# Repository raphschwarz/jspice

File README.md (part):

## JSpice for Mac

A native macOS app with a drag-and-draw schematic editor and live, real-time simulation (like iCircuit or Falstad) is in [`macos/`](macos/README.md).

## Introduction

JSpice is a SPICE-inspired analog circuit simulator made in Java with an emphasis on simulating memristors and analog circuits containing memristors. 

In a nutshell, JSpice is very limited compared to mainstream SPICE versions and only can do the following:

1. DC Operating Point Analysis
2. DC Sweep Analysis
3. Transient Analysis (Time response to arbitrary input waveform)

JSpice was originally written at a time before any mainstream SPICE applications supported simulation of memristors, and at that point we felt it would be easier to write a custom version of SPICE in Java rather than to try to figure out how to natively integrate memristor devices into existing SPICE versions. More recently, other, more capable simulators such as Xyce, have appeared with [native support for memristors](http://knowm.org/native-memristor-device-development-in-xyce/), and we are now leveraging those tools for CMOS + memristor circuit simulations.

JSpice is however still useful for rapid prototyping and serves as the simulation engine for [memristor-discovery](https://github.com/knowm/memristor-discovery). JSpice may interest you if you are interested in learning the mechanics of modified nodal analysis and your favorite programming langauge is Java. 

## Flow Chart of JSpice

Following is a simplified block diagram of the main JSpice program flow. 

)](documentation/SPICE_flow_chart.png)  

### In Words

- while the simulation is not over  
    * Formulate companion models for energy storage components, using current operating point  
    * Newton loop :  
        * while the convergence is not achieved  
            - Formulate companion models for non−linear components, using current operating point  
            - Solve for new operating point  
        * end while   
- end while  

([source](http://dev.hypertriton.com/edacious/trunk/doc/lec.pdf))

The heart of JSpice is matrix multiplication to solve the node values.

## Linear DC Operating Point Analysis

The core of any circuit simulation software is DC Operating Point Analysis. It's required for an initial solution to a Transient Analysis and also at each time step of a DC Sweep Analysis. All energy-storage components like capacitors, inductors and semiconductor charge mechanisms are ignored for this analysis. To perform a very basic DC Operating Point Analysis, the circuit Netlist needs to be loaded and parsed followed by solving linear nodal equations for voltage at each node:

1. Import Netlist
1. AC sources are zeroed out, capacitors are opened, and inductors are shorted
1. Use Kirchhoff's current law (KCL) to determine the algebraic sum of currents at each node
1. Using Linear Algebra, solve for the voltages at each node: G • v = i, where G is the conductance coefficients, v and i is the voltage and current at each node respectively.

A computerized circuit solver like SPICE doesn't start by writing nodal equations and converting them into a matrix. An advanced technique called Modified Nodal Analysis (MNA) is used. Each device has an MNA Stamp which is directly inserted into the impedance matrix (G) and the fixed source matrix (also called the right-hand-side matrix, RHS). Each voltage node and voltage source has a row/column pair and a slot in the RHS matrix. Each device is provided with pointers to locations in the matrix that it effects. That way a device doesn't have to have knowledge of the entire circuit, just the nodes it effects.

Like SPICE since version 3f5, JSpice uses MNA for Nodal Analysis, and it uses LUDecomposition to solve the systems of linear equations to determine the nodal values. For more information about MNA and MNA Stamps see the following links:

1. <http://users.ecs.soton.ac.uk/mz/CctSim/contents.htm>
1. <http://www.ece.iisc.ernet.in/~dipanjan/E8_262/E8262-CAD_4+5.pdf>
1. <http://qucs.sourceforge.net/tech/technical.html>
1. <http://dev.hypertriton.com/edacious/trunk/doc/lec.pdf>
1. <http://qucs.sourceforge.net/tech/node14.html>
1. <http://users.ecs.soton.ac.uk/mz/CctSim/chap1_3.htm>
1. <http://users.ecs.soton.ac.uk/mz/CctSim/chap1_4.htm>
1. <https://www.scribd.com/document/277142543/MNA-Stamp>

The above formulation of MNA can be applied to linear circuits only, but can extend to nonlinear. A linear circuit is an electronic circuit in which, for a sinusoidal input voltage of frequency f, any steady-state output of the circuit (the current through any component, or the voltage between any two points) is also sinusoidal with frequency f. Note that the output need not be in phase with the input.

The costs of the automatic circuit equation formulation:

1. To parse the Netlist : It consists in reading and storing the Netlist. O(N).
1. A topological analysis to build the unknowns vector: The Minimum Spanning Tree algorithm complexity is O(Nlog(N))
1. Stamping method: Each component writes its contribution in the table equation. O(N).
1. Matrix product: Multiplied two dense matrices costs O(N^3).

### Linear DC Operating Point Analysis Examples

#### I1R3 - One Current Source and Three Resistors

##### Code

Here, the `NetlistBuilder` pattern is demonstrated.

```java
public class DCOPI1R3 {

  public static void main(String[] args) {

    // run via NetlistBuilder
    NetlistBuilder builder = new NetlistBuilder().addNetlistDCCurrent("a", 1.0, "0", "1").addNetlistResistor("R1", 10, "1", "0")
        .addNetlistResistor("R2", 1000, "1", "2").addNetlistResistor("R3", 1000, "2", "0");
    Netlist netlist = builder.build();
    JSpice.simulate(netlist);
  }
}
```

##### Result

```
----nodes----
V(1) = 9.950248756218906
V(2) = 4.975124378109452
----components----
I(R1) = 0.9950248756218907
I(R2) = 0.004975124378109454
I(R3) = 0.004975124378109453
I(a) = 1.0
-------------
```

#### I1V1R6 -  One Current Source, One Voltage Source and Six Resistors

##### Code

Here, the `Netlist` is created as a stand-alone class, ideal for circuit reuse.

```java
public class DCOPI1V1R6 {

  public static void main(String[] args) {

    Netlist netlist = new I1V1R6();
    JSpice.simulate(netlist);
  }
}
```

```java
public class I1V1R6 extends Netlist {

  public I1V1R6() {

    // build netlist, the nodes can be named anything except for ground whose node is always labeled "0"
    addNetListComponent(new NetlistDCCurrent("a", 0.02, "0", "4"));
    addNetListComponent(new NetlistDCVoltage("x", 10.0, "2", "5"));
    addNetListComponent(new NetlistResistor("R1", 100, "5", "0"));
    addNetListComponent(new NetlistResistor("R2", 1000, "0", "3"));
    addNetListComponent(new NetlistResistor("R3", 1000, "2", "3"));
    addNetListComponent(new NetlistResistor("R4", 100, "1", "2"));
    addNetListComponent(new NetlistResistor("R5", 1000, "3", "0"));
    addNetListComponent(new NetlistResistor("R6", 10000, "1", "4"));
  }
}
```

##### Result

```
----nodes----
I(x) = 0.01250000000000003
V(1) = 13.250000000000005
V(2) = 11.250000000000004
V(3) = 3.750000000000001
V(4) = 213.25
V(5) = 1.2500000000000029
----components----
I(R1) = 0.012500000000000028
I(R2) = -0.0037500000000000007
I(R3) = 0.007500000000000002
I(R4) = 0.020000000000000018
I(R5) = 0.0037500000000000007
I(R6) = -0.02
I(a) = 0.02
-------------
```

## DC Sweep Analysis

DC Sweep Analysis is used to calculate a circuit’s bias point over a range of values. This procedure allows you to simulate a circuit many times, sweeping the DC values within a predetermined range. You can control the source values by choosing the start and stop values and the increment for the DC range. The bias point of the circuit is calculated for each value of the sweep.   

JSpice performs DC Sweep Analysis using the following process:

1. The DC Operating Point is calculated using a specified start value.
1. The value from the source is incremented and another DC Operating Point is calculated.
1. The increment value is added again and the process continues until the stop value is reached.
1. The result is displayed in a chart.

Assumptions: Capacitors are treated as open circuits, inductors as shorts. Only DC values for voltage and current sources are used.

All energy-storage components like capacitors, inductors and semiconductor charge mechanisms are ignored for this analysis. When time-varying components are present, their long-term behavior is approximated for example, capacitors become open circuits, and inductors become short circuits.

#### DC Sweep V1R4 - One Voltage Source and Four Resistors

##### Code

```java
public class DCSweepV1R4 {

  public static void main(String[] args) {

    Netlist netlist = new V1R4();
    netlist.setSimulationConfig(new DCSweepConfig("R1", "I(3)", 100.0, 10000, 100));
    JSpice.simulate(netlist);
  }
}
```

##### Result

## Non-Linear DC Operating Point Analysis

To simulate real circuits containing transistors and diodes, we are interested in simulating components having arbitrary i-v relations. We use the standard Newton method, described in any numerical analysis textbook. The derivation of how the multidimensional Newton method leads to our algorithm is a bit tedious, but here is an intuitive explanation : the Newton method works by linearizing the equation around the operating point Xn, solving the linearized equation to obtain Xn+1, and iterating until convergence (being when Xn is near Xn+1; the precise definition of near involving a compromise between speed and accuracy). In circuits, we linearize the i-v characteristic around point vn : i = i(vn)+(dv/di)(v−vn). That allows us to form companion models describing the linearized component, which we can stamp. The equation is then solved for another operating point, and the cycle continues until a stable answer is found.

### PN Diode Companion Model

)](documentation/PN_Diode_Model.png)  

#### DCSweepV1D1 - One Voltage Source and One Diode

##### Code

```java
public class DCSweepV1D1 {

  public static void main(String[] args) {

    Netlist netlist = new V1D1();
    netlist.setSimulationConfig(new DCSweepConfig("Va", "I(D1)", 0.5, .95, .005));
    JSpice.simulate(netlist);
  }
}
```

##### Result

### MOSFET NMOS Companion Model

)](documentation/NMOS_Model.png)  

#### DCSweepV2NMOS1 - Two Voltage Sources and One NMOS

##### Code

```java
public class DCSweepV2NMOS1 {

  public static void main(String[] args) {

    // Circuit
    Netlist netlist = new V2NMOS1();

    // SweepDef
    DCSweepConfig sweepDef1 = new DCSweepConfig("Vdd", "I(NMOS1)", 0.0, 10.0, 0.1);
    DCSweepConfig sweepDef2 = new DCSweepConfig("Vg", "I(NMOS1)", 0.0, 5.0, 1.0);

    // run DC sweep
    DCSweep dcSweep = new DCSweep(netlist);
    dcSweep.addSweepConfig(sweepDef1);
    dcSweep.addSweepConfig(sweepDef2);
    SimulationResult dcSweepResult = dcSweep.run("I(NMOS1)");

    // plot
    SimulationPlotter.plotAll(dcSweepResult);

  }
}
```

##### Result

### MOSFET PMOS Companion Model

)](documentation/PMOS_Model.png)  

#### DCSweepV2PMOS1 - Two Voltage Sources and One PMOS

##### Code

```java
public class DCSweepV2PMOS1 {

  public static void main(String[] args) {

    // Circuit
    Netlist netlist = new V2PMOS1();

    // SweepDef
    DCSweepConfig sweepDef1 = new DCSweepConfig("Vg", "I(PMOS1)", -5.0, 0.0, 1.0);
    DCSweepConfig sweepDef2 = new DCSweepConfig("Vdd", "I(PMOS1)", -10.0, 0.0, 0.1);

    // run DC sweep
    DCSweep dcSweep = new DCSweep(netlist);
    dcSweep.addSweepConfig(sweepDef2);
    dcSweep.addSweepConfig(sweepDef1);
    SimulationResult dcSweepResult = dcSweep.run("I(PMOS1)");
    System.out.println(dcSweepResult.toString());

    // plot
    SimulationPlotter.plotAll(dcSweepResult);
  }
}
```

##### Result

#### CMOSInverter

##### Code

```java
public class DCSweepCMOSInverter {

  public static void main(String[] args) {

    Netlist netlist = new CMOSInverterCircuit();
    netlist.setSimulationConfig(new DCSweepConfig("Vin", "V(out)", 0, 5, .10));
    JSpice.simulate(netlist);
  }
}
```

##### Result

## Transient Analysis

In Transient Analysis, also called time-domain transient analysis, JSpice computes the circuit’s response as a function of time. This analysis divides the time into segments and calculates the voltage and current levels for each given interval. Finally, the results, voltage versus time, are plotted.

JSpice performs Transient Analysis using the following process:

Each input cycle is divided into intervals.
A DC Operating Point Analysis is performed for each time point in the cycle.
The solution for the voltage waveform at a node is determined by the value of that voltage at each time point over one complete cycle.

Assumptions: DC sources have constant values; AC sources have time-dependent values. Capacitors and inductors are represented by energy storage models. Numerical integration is used to calculate the quantity of energy transfer over an interval of time.

Let's see how numeric integration for a capacitor works. Knowing a function at some point in time `tn`, how could you approximate the function at a future time point `tn+1`? Here's one approach. What if you looked to the slope of the curve to tell you, at least locally, where the voltage is going? Then, simply multiply the slope by the time step `h = Δt = tn+1 - tn` and add it to the present voltage - that should get you in the neighborhood at least.

The FE formula is so intuitive, but its not the best method. Another method, the backward- Euler (BE), uses the slope at `xn+1`, rather than the one at `xn`, to predict the next voltage.

Okay, we're approaching our overall goal of transforming an energy-storage component into its equivalent linear components. For example, a capacitor is transformed using a two step process:

Step 1. Apply numeric integration to the current-versus-voltage relationship of a capacitor.
Step 2. Use the result to develop a linear companion memristor well-suited for Nodal Analysis to calculate the circuit's output waveform.

Long story short, given the time step size (`h`) and the voltage across the capacitor at a certain time point, the capacitor is replaced in the circuit with the following linear companion memristor consisting of a Resistor and a current source. JSpice then carries out it's nodal analysis as before.

)](documentation/Capacitor_Model.png)  

### Drivers

The following time-based drivers are available: DC, Sine, Triangle, Sawtooth, Square, Pulse, Arbitrary, and Streaming Arbitrary. Most Drivers take the following arguments during creation:

* Name
* DC Offset
* Phase
* Amplitude
* Frequency

#### DC
    Driver driver = new DC("Vdc", 2.5);

#### Sine
    Driver sine = new Sine("Sine", 5, Math.PI / 4, 10, 2);

#### Triangle
    Driver driver = new Triangle("Triangle", 5, 0.25, 10, 2);

#### Sawtooth
    Driver driver = new Sawtooth("Sawtooth", 5, .25, 10, 2);

#### Square
    Driver driver = new Square("Square", 5, .2, 10, .5); // unit test case

#### Pulse
    Driver driver = new Pulse("Pulse", 5, .2, 10, .5, .10); // unit test case

#### Arbitrary
    Driver driver = new Arbitrary("Arbitrary", 0, 0, 1, 1.0, new double[] { .1, .2, .5, .6 });

#### Arbitrary Streaming
    Driver driver = new StreamingArbitrary("Arbitrary Streaming", 0, 0, 1, 1.0, new double[] { .1, .2, .5, .6 }, new String[] { "1", "0", "1" });

#### CMOS Inverter with Triangle Driver

##### Code

```java
public class TransientAnalysisCMOSInverter {

  public static void main(String[] args) {

    Netlist netlist = new CMOSInverterCircuit();
    TransientConfig transientConfig = new TransientConfig(2, .05, new Triangle("Vin", 2.5, 0, 2.5, 1.0));
    netlist.setSimulationConfig(transientConfig);
    SimulationResult simulationResult = JSpice.simulate(netlist);
    SimulationPlotter.plot(simulationResult, "V(in)", "V(out)");
  }
}
```

##### Result

#### RC Circuit with Square Driver

##### Code

```java
public class TransientAnalysisV1R1C1 {

  public static void main(String[] args) {

    Netlist netlist = new V1R1C1();
    TransientConfig transientConfig = new TransientConfig(2, .01, new Square("V1", 2.5, 0, 2.5, 1.0));
    netlist.setSimulationConfig(transientConfig);
    SimulationResult simulationResult = JSpice.simulate(netlist);
    SimulationPlotter.plot(simulationResult, new String[]{"V(1)", "V(2)"});
  }
}
```

##### Result

#### Half-Wave Rectifier with Sine Driver

##### Code

```java
public class TransientAnalysisHalfWaveRectifier {

  public static void main(String[] args) {

    Netlist netlist = new HalfWaveRectifier();
    TransientConfig transientConfig = new TransientConfig(.0833333333, .0002, new Sine("Vsrc", 0, 0, 12, 60.0));
    netlist.setSimulationConfig(transientConfig);
    SimulationResult simulationResult = JSpice.simulate(netlist);
    SimulationPlotter.plot(simulationResult, "V(in)", "V(out)");
  }
}
```

##### Result

#### Pass Gate (Transmission Gate)

##### Code

```java
public class TransientAnalysisTransmissionGate {

  public static void main(String[] args) {

    Netlist netlist = new TransmissionGateCircuit();

    Driver in = new Sine("Vin", 0, 0, 1.0, 10.0);
    Driver clk = new Square("Vclk", 2.5, 0, 2.5, 1.0);
    Driver clkBar = new Square("VclkBar", 2.5, 0.5, 2.5, 1.0);

    TransientConfig transientConfig = new TransientConfig(2, .005, in, clk, clkBar);
    netlist.setSimulationConfig(transientConfig);
    SimulationResult simulationResult = JSpice.simulate(netlist);
    SimulationPlotter.plotSeparate(simulationResult, "V(out)", "V(in)", "V(CLK)", "V(CLKBAR)");
  }
}
```

##### Result

## M-MSS Memristor Simulation

### Simple Hysteresis Curves

#### M-MSS Memristor Model Driven by Square Wave

##### Code

```java
public class TransientAnalysisV1MMSSMem {

  public static void main(String[] args) {

    Netlist netlist = new V1MMSSMem();
    TransientConfig transientConfig = new TransientConfig(.04, .0001, new Sine("Vdd", 0.0, 0, 0.5, 100.0));
    netlist.setSimulationConfig(transientConfig);
    SimulationResult simulationResult = JSpice.simulate(netlist);
    SimulationPlotter.plotSeparate(simulationResult, new String[]{"V(VDD)", "I(M1)"});
    SimulationPlotter.plotTransientInOutCurve("I/V Curve", simulationResult, new String[]{"V(VDD)", "I(M1)"});

  }
}
```

##### Result

## RS(Really Simple) Memristor Simulation

### Current vs. Time

#### RS Memristor Model Driven by Square Wave

##### Code

Option #1: `NetlistBuilder`

```java
public class TransientAnalysisRSMem {

  private final static double schottkeyAlpha = 0; // N/A
  private final static double schottkeyBeta = 0; // N/A
  private final static double phi = 1;

  public static void main(String[] args) throws IOException, ConfigurationException {

    // run via NetlistBuilder
    NetlistBuilder builder = new NetlistBuilder().addNetlistDCVoltage("Vdd", 1.0, "VDD", "0")
        .addNetlistRSMemristor("M1", schottkeyAlpha, schottkeyBeta, schottkeyAlpha, schottkeyBeta, phi, "VDD", "0")
        .addTransientSimulationConfig(1.0E-3, 1E-5, new Sine("Vdd", 0.0, 0, 1.2, 2000.0));
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
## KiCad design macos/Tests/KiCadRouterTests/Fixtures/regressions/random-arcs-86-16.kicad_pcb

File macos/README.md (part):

# JSpice for Mac

A native macOS circuit simulator in the spirit of iCircuit and the Falstad applet: draw a circuit and watch it run live, with voltages shown as colour and current as moving dots.

## Features

- **Fast, keyboard-first editing.** Every part has a shortcut (a letter for the common ones, ⇧ and a letter for the rest; they are shown in the library and in Help ▸ Keyboard Shortcuts, ⌘/). ⌘K or / opens a palette: type a part's name, its category or a real part it models ("TL072", "LM13700", "vactrol") and press Return. While placing, a ghost of the part follows the pointer and a pill says what you are placing. Arrow keys nudge the selection (⇧ for five units), ⌘D duplicates it, Tab steps through the parts, and the library can be searched.
- **Draw circuits directly.** Pick a part in the library (or press its key: `R` resistor, `C` capacitor, `W` wire, …), then click to place it or drag to set its length and direction. Parts connect where their ends meet, and a part dropped onto the middle of a wire joins it with a T-junction (wires that merely cross stay apart). Wires stretch when you move the parts they connect.
- **Live simulation.** The circuit simulates while you draw. Voltages are coloured (green positive, red negative, grey at 0 V), current flows as dots, LEDs and lamps glow, and memristors show their internal state.
- **Real time when possible.** Circuits that change slowly enough to watch run in real time (a capacitor charging over a second, a 1 Hz memristor loop). Faster ones run in slow motion automatically, for example a 100 Hz filter at 5 ms per second, and the status bar says so. If a circuit is too heavy to keep up, it runs as fast as it can and the status bar shows how far behind it is. You can also set the speed yourself.
- **Interact while it runs.** Click switches, hold push buttons, scroll over a potentiometer to turn it, and drag sliders in the inspector to change values live.
- **Hear it.** Put a speaker across an output and press **Sound** in the toolbar: the circuit runs in real time, one simulation step per audio sample, on a thread of its own, and you hear it through the Mac's output (with a DC blocker and a soft limit, so a stuck rail is silent and nothing clips harshly). Turn a potentiometer or flip a switch while it plays. The speaker's **full scale** sets the voltage that plays at full volume.
- **Play sound into it.** The **Audio In** source (⇧P) plays a sound into the circuit: a built-in guitar riff, any sound file macOS can read (WAV, AIFF, MP3, AAC…, mixed to mono, up to a minute, kept in the circuit file) chosen in the inspector, once or looped, or the Mac's **live input** while sound is on, so a guitar through an audio interface plays the circuit in real time. Its **level** is the voltage of full scale (0.5 V by default, about a guitar's pickup). **File ▸ Export Sound…** renders the speaker to a 24-bit WAV file offline, as long as you like and however heavy the circuit is, through the same DC blocker and soft limit as the live sound. The **Fuzz Face on a guitar riff** example puts it together.
- **Play it.** The **Keyboard Pitch** source puts out 1 V per octave (0 V at C2) and the **Keyboard Gate** source a gate while a key is held. With sound on, play them from the Mac's keyboard (A W S E D F T G Y H U J K O L P ; as in GarageBand; Z and X change octave) or from any MIDI keyboard (notes and pitch bend). The newest key sounds, and the pitch stays on the last note after release; give the pitch some **glide** for portamento. A **step sequencer** (in the inspector when the circuit has a keyboard source) plays them by itself: up to 32 steps of notes or rests at a sixteenth note each, with tempo and gate length; it keeps time with the circuit, so it is exact with sound on and in automated simulations. The **Keyboard VCO** example is a real 1 V/octave oscillator (a PNP exponential converter and an LM13700 triangle core), and **Mono synth** plays its square wave through an LM13700 VCA opened by an attack–release envelope (the gate charges it through a DG411 switch).
- **Front panel.** Below the schematic, the circuit's potentiometers, switches and push buttons appear as hardware controls on a faceplate, like a plugin's interface for testing an audio circuit: knobs to drag (double-click to centre), bat toggles to flip, buttons to hold, LEDs as panel lamps, and a level meter for the speaker that turns red when the sound clips. Double-click a label to rename the part. Toggle it with **Panel** in the toolbar.
- **MIDI Learn.** Right-click a knob, switch or button (on the front panel or the schematic), choose **MIDI Learn** and move a knob, fader or button on a MIDI controller: from then on it turns that knob (across its whole travel) or flips that switch (on from 64 up), knobs inside blocks too. The mapping is saved with the circuit and shown under the control; **Forget** takes it away, Esc cancels learning.
- **Scopes** for any part's voltage, current, power or resistance over time, or its current against its voltage (an I–V curve, such as a memristor's pinched hysteresis loop).
- **Knob sweep.** On a frequency response (or a loop probe's loop gain), choose a knob under **Sweep** to draw the response with that knob at 0, 25, 50, 75 and 100 % as well, coloured from blue to orange under the response as the knob is now: a tone control's whole range, or a gain knob's effect on a loop's phase margin (the legend gives each position's margin), at a glance. Each position is a copy of the circuit settled from rest with the knob there (so a knob that sets a bias moves the operating point too) and linearised in the background; the readout under the pointer gives each position's gain. Knobs inside blocks can be swept too. The `sweep` tool does the same for an agent (`"parameter": "position"` with an `ac` measure).
- **Knob movement.** A potentiometer's inspector has **Movement**: **Move back and forth** turns the knob from one position to the other and back by itself, once every quarter second to 16 s, slowing at each end as a foot rocks a wah pedal, while you listen and watch the scopes; **From** and **To** set its range. Right-click a knob on the front panel for **Move Back and Forth** too. It goes back where it was when it stops, and **File ▸ Export Sound…** records it moving. `simulate` and `render_audio` take `"knobs": [{"part": "WAH", "period": 2, "low": 0, "high": 1}]` for the same, the knobs moving every millisecond of circuit time.
- **Tolerances.** Tick **Tolerances** on a frequency response to shade where 24 copies of the circuit fall, their resistors drawn within 5 %, capacitors and inductors within 10 % and transistors' gain within 30 % (normally distributed, three standard deviations at the tolerance), each copy settled and linearised in the background. The `sweep` tool steps a value and measures each step; `monte_carlo` measures hundreds of copies (gain and phase, the peak and the corner, an operating point, or a waveform's level and frequency) and gives the spread, with tolerances of your choosing, part by part if need be.
- **Noise.** The frequency response also gives the noise at that output from 20 Hz to 20 kHz (and which part makes most of it), and the `noise` tool gives it frequency by frequency, referred to the input too: every resistor's thermal noise, every junction's shot noise, the channel noise of field-effect transistors, tubes' noise and op-amps' input noise (TL072 18 nV/√Hz, NE5532 5, LM358 40), carried to the output through the linearised circuit, as SPICE's `.noise` does. One solve of the transposed equations per frequency gives how a current anywhere reaches the output, so all the sources cost one solve. It matches ngspice's `.noise` within 0.01 dB.
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
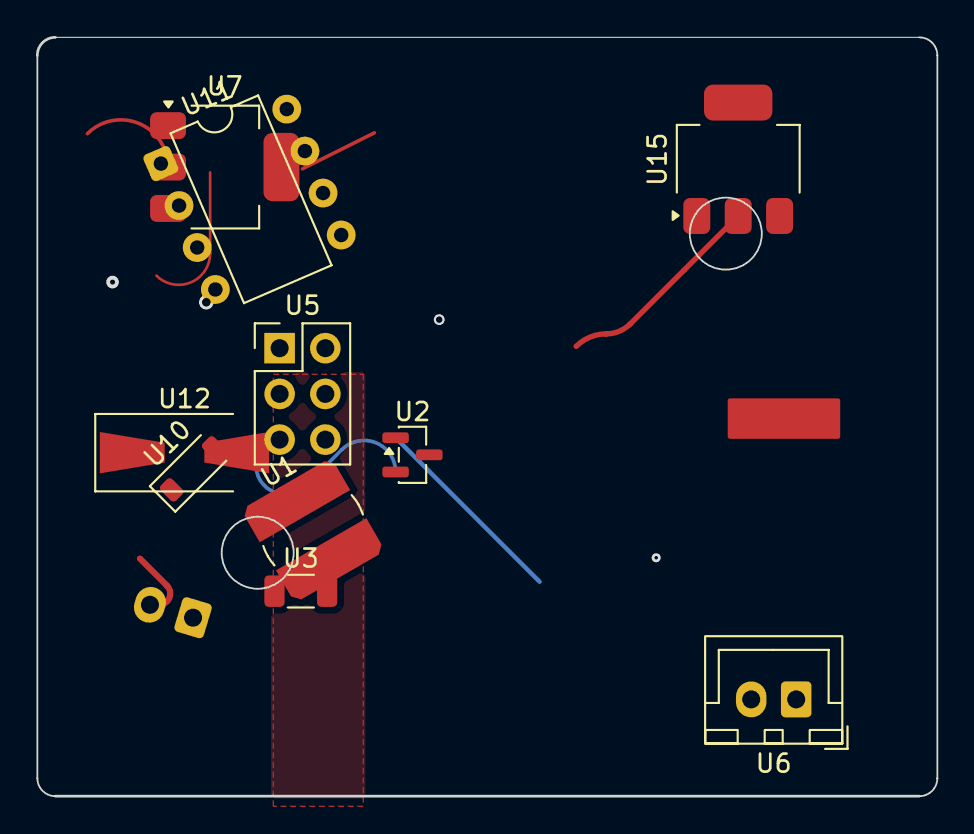
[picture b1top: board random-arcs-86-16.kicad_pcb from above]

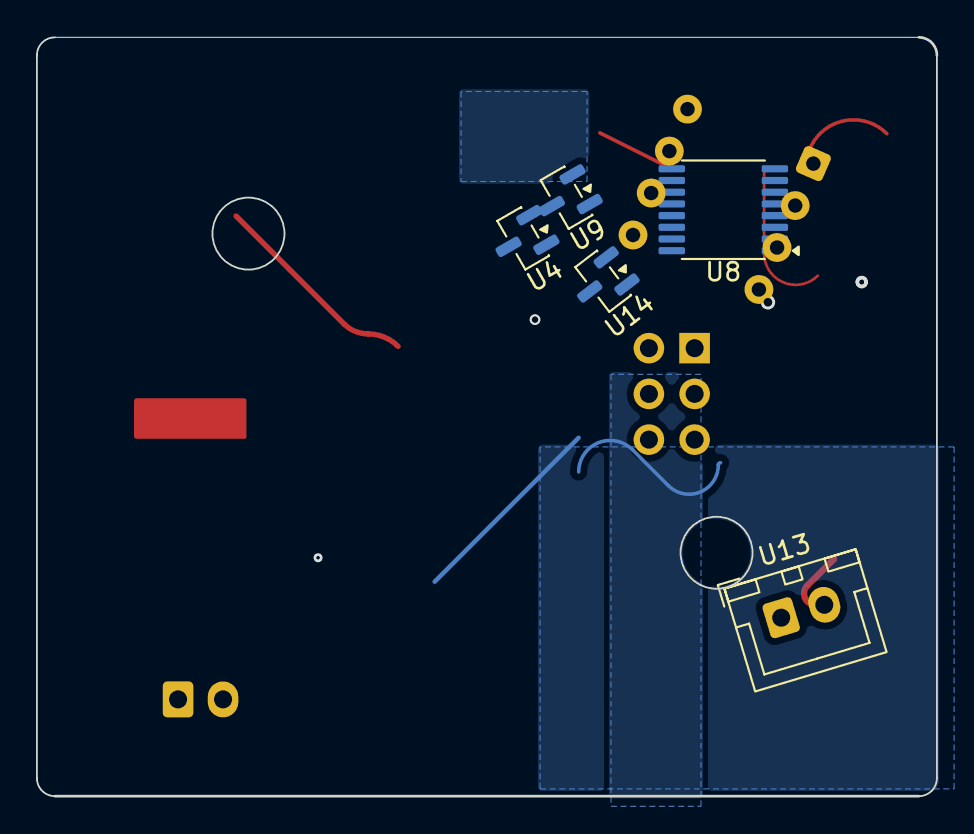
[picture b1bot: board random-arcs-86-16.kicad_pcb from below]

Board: 2 copper layers, 50.0 x 42.2 mm, 15 parts (5 on the bottom side), 6 nets.

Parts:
U1: L_Bourns_SDR0604
U2, U4, U9, U14: SOT-23
U3: R_1206_3216Metric
U5: PinHeader_2x03_P2.54mm_Vertical
U6, U13: JST_XH_B2B-XH-A_1x02_P2.50mm_Vertical
U7, U15: SOT-223-3_TabPin2
U8: TSSOP-16_4.4x5mm_P0.65mm
U10: D_SOD-123
U11: DIP-8_W7.62mm
U12: D_SMA-SMB_Universal_Handsoldering

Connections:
/net3: U7.2, U8.6, U8.9, U8.16, U10.1, U10.2, U11.2, U11.8
D7: U2.2, U4.3, U6.1, U6.2, U8.5, U13.1, U15.1, U15.3
GND: U2.1, U4.2, U5.6, U8.1, U8.13, U11.3, U11.5, U12.2
PWR1: U2.3, U3.1, U3.2, U7.2, U8.2, U8.3, U8.4, U8.7, U8.8, U8.10, U8.12, U8.14, U9.2, U11.6, U12.1, U14.1, U14.2
SIG2: U5.3, U5.5, U7.1, U9.1
VCC: U5.2, U8.11, U15.2

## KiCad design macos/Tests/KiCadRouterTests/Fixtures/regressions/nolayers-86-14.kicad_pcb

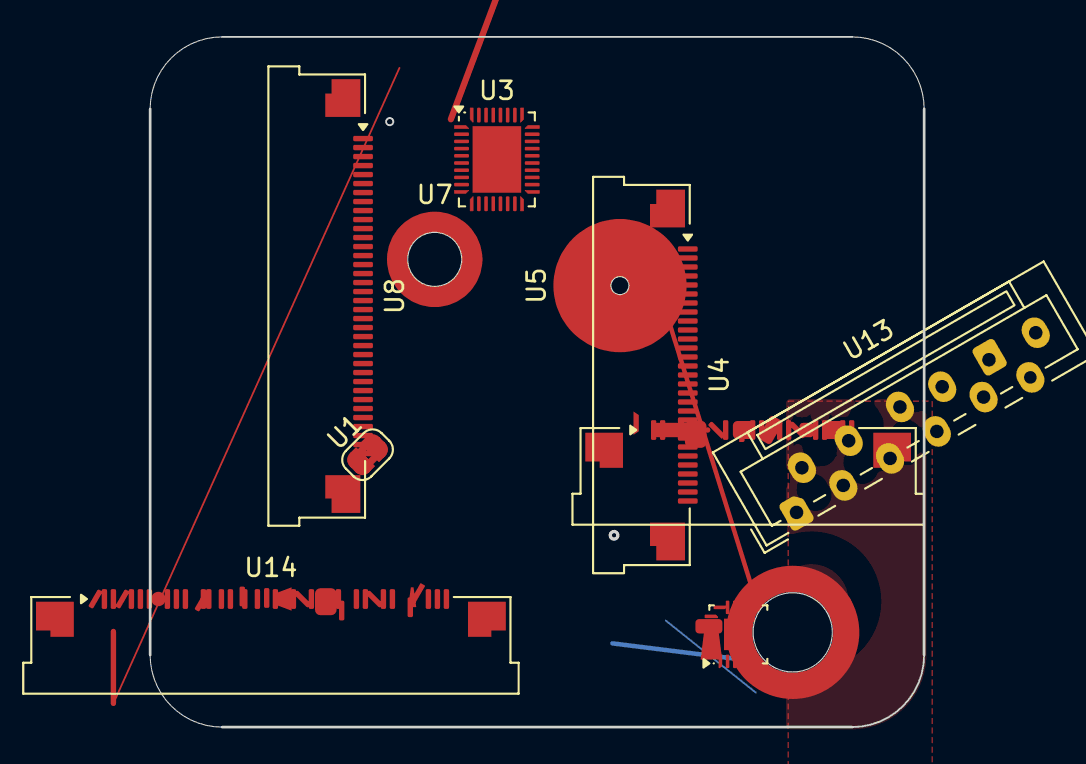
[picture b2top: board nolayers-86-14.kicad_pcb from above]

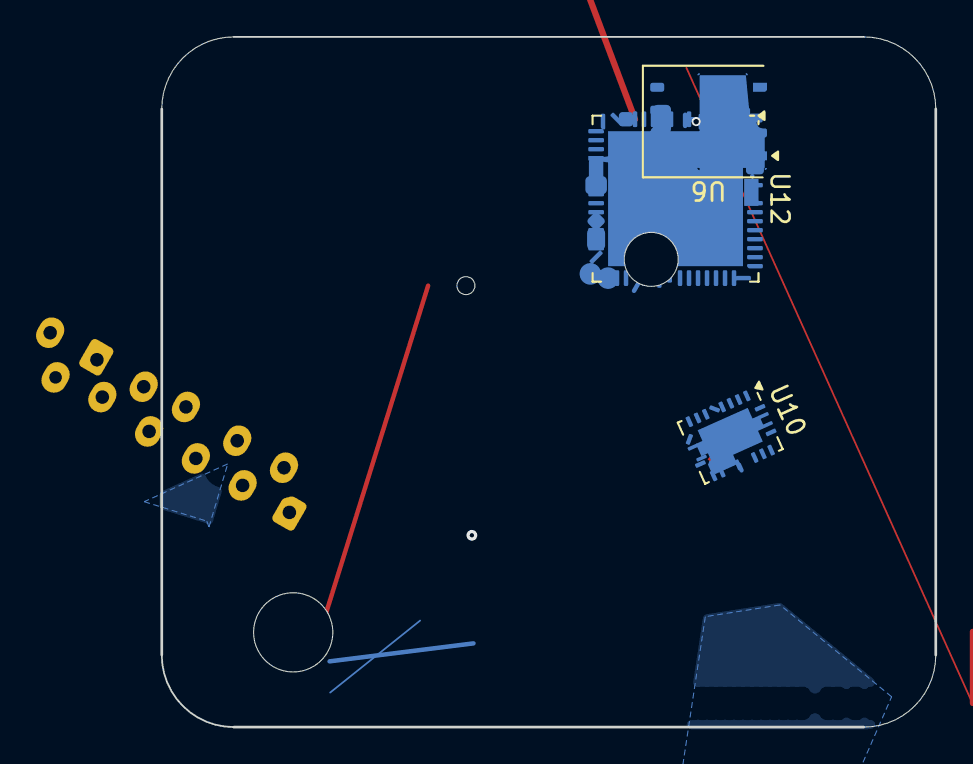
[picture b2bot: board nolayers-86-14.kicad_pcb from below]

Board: 2 copper layers, 43.0 x 38.3 mm, 14 parts (3 on the bottom side), 9 nets.

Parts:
U1: SolderJumper-2_P1.3mm_Bridged2Bar_RoundedPad1.0x1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; SolderJumper-2_P1.3mm_Bridged2Bar_RoundedPad1.0x1.5mm
U2: JSpice "edited"; QFN-24-1EP_3x3mm_P0.4mm_EP1.75x1.6mm
U3: Texas_REE0036A_WQFN-36-1EP_4x5mm_P0.4mm_EP2.7x3.7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; Texas_REE0036A_WQFN-36-1EP_4x5mm_P0.4mm_EP2.7x3.7mm
U4: Amphenol_F32R-1A7x1-11029_1x29-1MP_P0.5mm_Horizon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; Amphenol_F32R-1A7x1-11029_1x29-1MP_P0.5mm_Horizontal
U5: Mounting_Wuerth_WA-SMSE-ExternalM3_H14mm_97711403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; Mounting_Wuerth_WA-SMSE-ExternalM3_H14mm_9771140360
U6: ST_PowerFLAT_HV-8_5x6mm
U7: Mounting_Wuerth_WA-SMSI-M2_H4.5mm_9774045243
U8: Amphenol_F32R-1A7x1-11036_1x36-1MP_P0.5mm_Horizon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; Amphenol_F32R-1A7x1-11036_1x36-1MP_P0.5mm_Horizontal
U9: JSpice "edited"; Amphenol_F32Q-1A7x1-11024_1x24-1MP_P0.5mm_Horizontal
U10: Texas_VQFN-RHL-20
U11: JSpice "edited"; Mounting_Wuerth_WA-SMSR-3.2mm_H5.1mm_ReverseMount_9775051960
U12: QFN-64-1EP_9x9mm_P0.5mm_EP7.5x7.5mm
U13: JST_ZE_B12B-ZESK-D_1x12_P1.50mm_Vertical
U14: 4.7µF; Amphenol_F32Q-1A7x1-11040_1x40-1MP_P0.5mm_Horizontal

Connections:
/net3: U2.5, U2.8, U3.13, U3.15, U3.27, U4.1, U4.8, U4.21, U4.23, U7.1, U8.20, U8.35, U8.MP, U9.1, U9.22, U10.13, U11.1, U12.2, U12.13, U12.15, U12.49, U12.55, U14.1, U14.29, U14.31
D7: U2.1, U3.2, U3.6, U3.23, U3.32, U4.11, U5.1, U6.4, U6.8, U7.1, U8.18, U8.33, U9.4, U9.MP, U10.21, U11.1, U12.4, U12.27, U12.33, U12.35, U12.39, U12.52, U12.63, U13.3, U14.33
GND: U2.6, U3.8, U3.9, U3.16, U3.18, U3.21, U3.31, U3.37, U4.15, U4.27, U8.11, U8.12, U8.26, U9.2, U10.1, U10.2, U10.6, U10.15, U10.20, U12.18, U12.34, U12.45, U12.A1, U12.EP, U13.7, U14.2, U14.3, U14.11, U14.15, U14.17, U14.A1
N1: U2.14, U2.18, U3.1, U3.30, U4.3, U4.24, U5.1, U6.5, U8.10, U8.23, U8.28, U8.30, U9.5, U9.10, U10.19, U12.10, U12.11, U12.30, U12.58, U12.EP, U13.9, U14.21
N3: U3.7, U3.24, U3.29, U4.12, U4.17, U4.29, U5.1, U6.3, U8.34, U9.13, U10.17, U10.21, U12.19, U12.43, U12.44, U12.53, U12.56, U12.59, U12.EP, U14.13, U14.16, U14.20, U14.28, U14.35, U14.A1
PWR1: U2.EP, U3.3, U3.33, U4.7, U4.9, U4.13, U4.16, U4.26, U6.2, U8.1, U8.22, U9.3, U10.10, U10.EP, U12.9, U12.24, U12.28, U12.51, U12.60, U12.64, U13.1, U14.6, U14.9, U14.10, U14.22, U14.36, U14.MP
PWR_5V: U2.13, U2.17, U2.21, U3.19, U3.25, U4.6, U4.22, U4.MP, U5.1, U8.2, U8.4, U8.14, U8.16, U8.24, U8.27, U8.29, U9.18, U10.5, U10.7, U10.21, U12.1, U12.26, U12.50, U12.54, U12.61, U13.8, U14.1, U14.14, U14.24, U14.27, U14.37
SIG1: U1.1, U2.1, U2.2, U2.4, U3.10, U3.20, U3.34, U4.10, U4.14, U4.28, U8.5, U8.8, U8.MP, U9.1, U9.6, U9.11, U9.17, U9.20, U9.21, U10.3, U10.18, U11.1, U12.7, U12.14, U12.29, U12.31, U12.47, U13.12, U14.23, U14.34, U14.A1
SIG2: U2.24, U3.4, U3.5, U3.26, U4.18, U6.1, U8.32, U8.36, U9.24, U10.4, U10.9, U10.11, U12.8, U12.16, U12.17, U12.36, U12.38, U14.8, U14.30

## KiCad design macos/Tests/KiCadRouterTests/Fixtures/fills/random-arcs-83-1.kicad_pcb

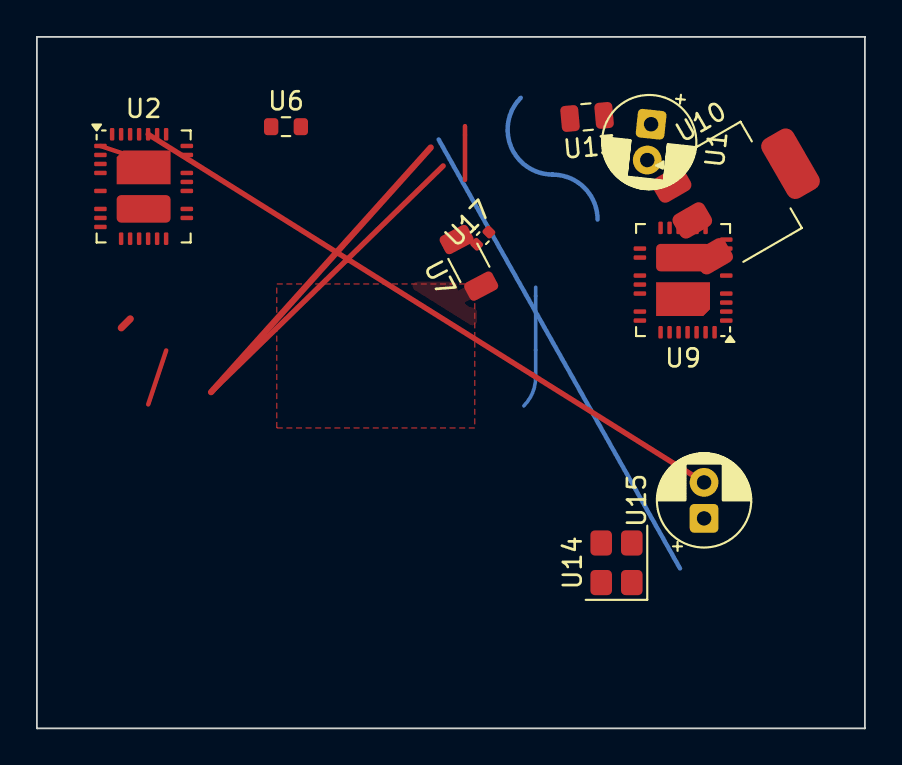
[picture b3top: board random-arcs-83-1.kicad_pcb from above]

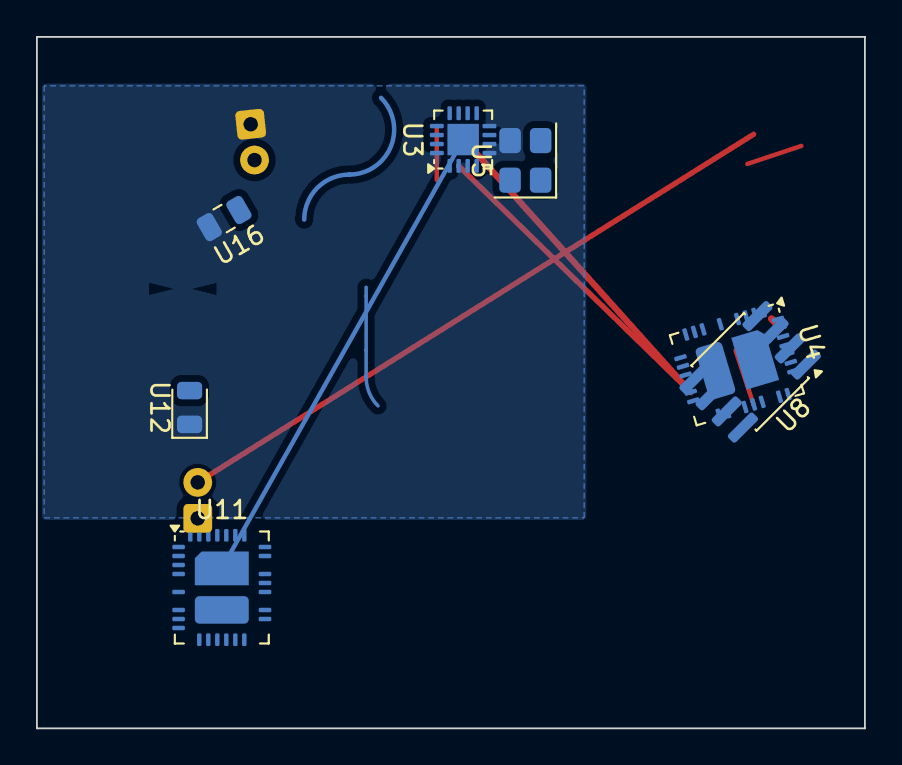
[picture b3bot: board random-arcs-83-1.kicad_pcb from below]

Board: 2 copper layers, 46.0 x 38.4 mm, 17 parts (7 on the bottom side), 6 nets.

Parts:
U1, U15: CP_Radial_D5.0mm_P2.00mm
U2, U4, U9, U11: Analog_QFN-28-36-2EP_5x6mm_P0.5mm
U3: QFN-16-1EP_3x3mm_P0.5mm_EP1.75x1.75mm
U5, U14: Crystal_SMD_3225-4Pin_3.2x2.5mm
U6: R_0603_1608Metric
U7: R_1206_3216Metric
U8: SOIC-8_3.9x4.9mm_P1.27mm
U10: SOT-223-3_TabPin2
U12: LED_0805_2012Metric
U13, U16: C_0805_2012Metric
U17: C_0402_1005Metric

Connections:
/net3: U1.1, U2.2, U2.4, U2.8, U2.17, U2.23, U2.32, U3.2, U3.3, U3.5, U3.6, U3.8, U3.16, U4.15, U4.16, U4.17, U4.24, U4.30, U5.3, U7.1, U9.6, U9.9, U9.33, U10.2, U11.3, U11.20, U12.1, U13.1, U16.2
/sub/clk: U2.3, U2.12, U3.11, U4.2, U4.34, U4.38, U9.2, U9.12, U9.34, U11.2, U11.14, U11.23, U14.4, U15.1
GND: U2.6, U2.21, U2.35, U2.36, U4.3, U4.6, U4.14, U4.25, U4.32, U4.36, U4.37, U5.4, U6.2, U8.4, U8.6, U9.4, U9.10, U9.16, U9.27, U10.3, U11.1, U11.4, U11.6, U11.10, U11.24, U11.33, U12.2, U13.2, U14.1, U16.1
N2: U1.2, U2.15, U2.27, U2.28, U2.33, U2.34, U2.38, U3.1, U3.4, U4.9, U4.10, U4.12, U4.20, U4.21, U4.35, U5.1, U6.1, U8.1, U8.3, U8.7, U8.8, U10.2, U11.16, U11.21, U11.30, U15.2
N3: U2.13, U2.25, U2.31, U4.4, U4.31, U5.2, U9.15, U9.31, U9.35, U11.13, U11.25, U11.36, U14.3
PWR1: U2.1, U2.10, U2.16, U2.20, U3.12, U3.13, U9.1, U9.13, U9.20, U9.25, U9.32, U11.15, U11.32, U11.35, U14.2

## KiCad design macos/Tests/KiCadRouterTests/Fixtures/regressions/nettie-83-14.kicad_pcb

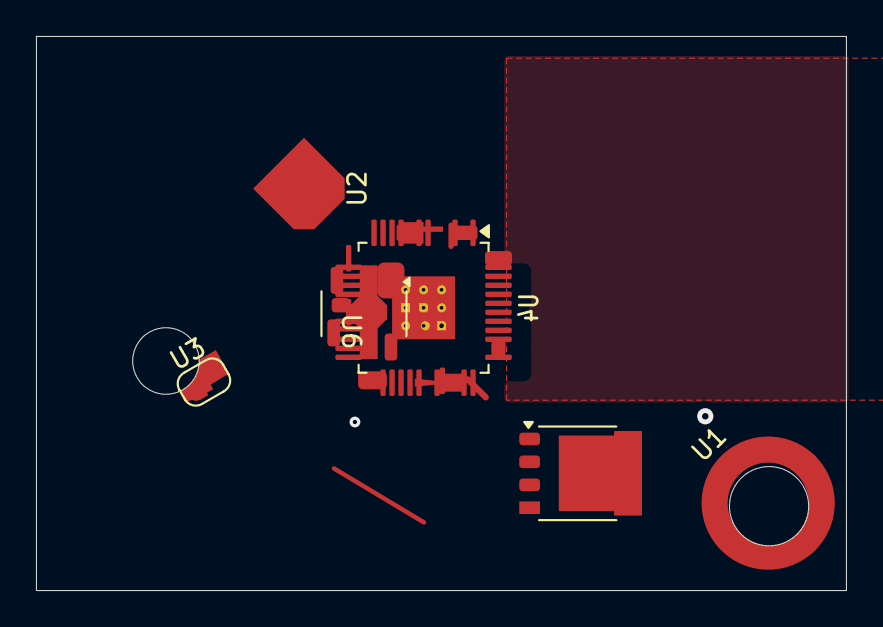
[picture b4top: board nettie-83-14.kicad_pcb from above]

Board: 2 copper layers, 45.0 x 30.8 mm, 7 parts (1 on the bottom side), 8 nets.

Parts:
4.7µF: JSpice "edited"; LFPAK56
U1: Mounting_Wuerth_WA-SMSR-M3_H11.6mm_ReverseMount_9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; Mounting_Wuerth_WA-SMSR-M3_H11.6mm_ReverseMount_9775116360
U2: Mounting_Wuerth_WA-SMSI-M1.6_H6mm_ThreadDepth2mm_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; Mounting_Wuerth_WA-SMSI-M1.6_H6mm_ThreadDepth2mm_NoNPTH_977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
U3: SolderJumper-2_P1.3mm_Bridged2Bar_RoundedPad1.0x1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; SolderJumper-2_P1.3mm_Bridged2Bar_RoundedPad1.0x1.5mm
U4: TQFP-48-1EP_7x7mm_P0.5mm_EP3.5x3.5mm_ThermalVias
U5: Mounting_Wuerth_WA-SMST-2.7mm_H2.5mm_9774025951
U6: SOT-89-5

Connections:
/sub/clk: U4.5, U4.6, U4.36, U4.49, U6.3
D7: 4.7µF.1, 4.7µF.5, U4.17, U4.49, U4.A1
D12: 4.7µF.3, U2.1, U3.EP, U4.24, U4.39, U4.47, U4.49, U4.EP, U5.1, U6.1
N1: U4.1, U4.14, U4.28, U4.31, U4.44, U4.49
N2: U1.1, U4.15, U4.16, U4.18, U4.41, U4.43
PWR_5V: 4.7µF.4, U4.2, U4.13, U4.23, U4.26, U4.33, U4.34, U4.35, U6.5
SIG1: U1.1, U4.11, U4.25, U4.46, U4.49, U4.EP, U5.1, U6.4
VCC: 4.7µF.2, U3.2, U4.9, U4.27, U4.48, U6.2

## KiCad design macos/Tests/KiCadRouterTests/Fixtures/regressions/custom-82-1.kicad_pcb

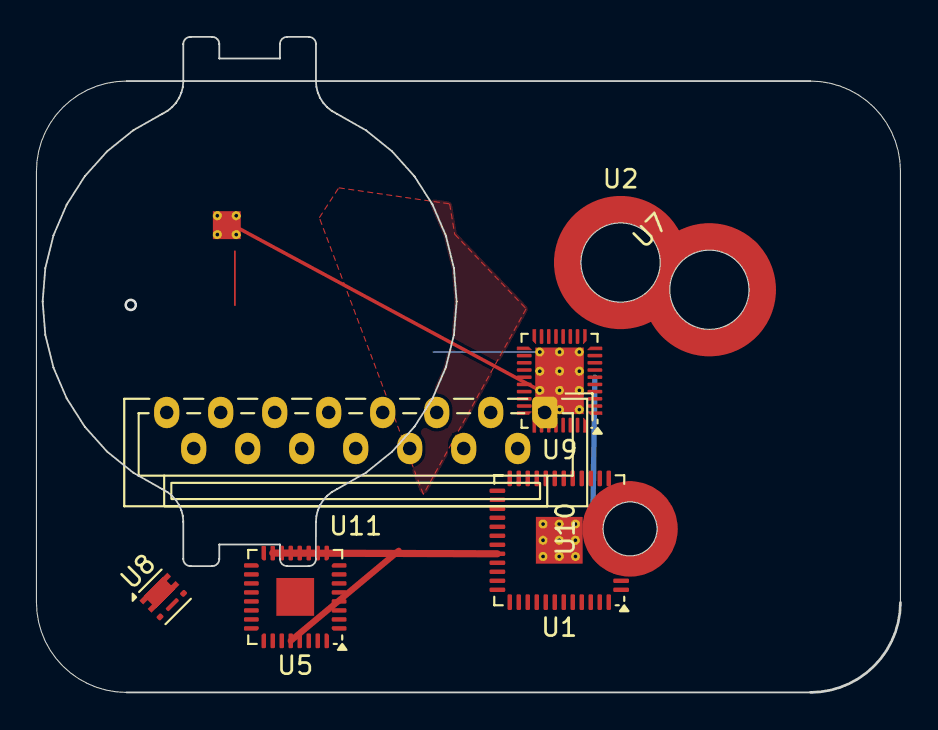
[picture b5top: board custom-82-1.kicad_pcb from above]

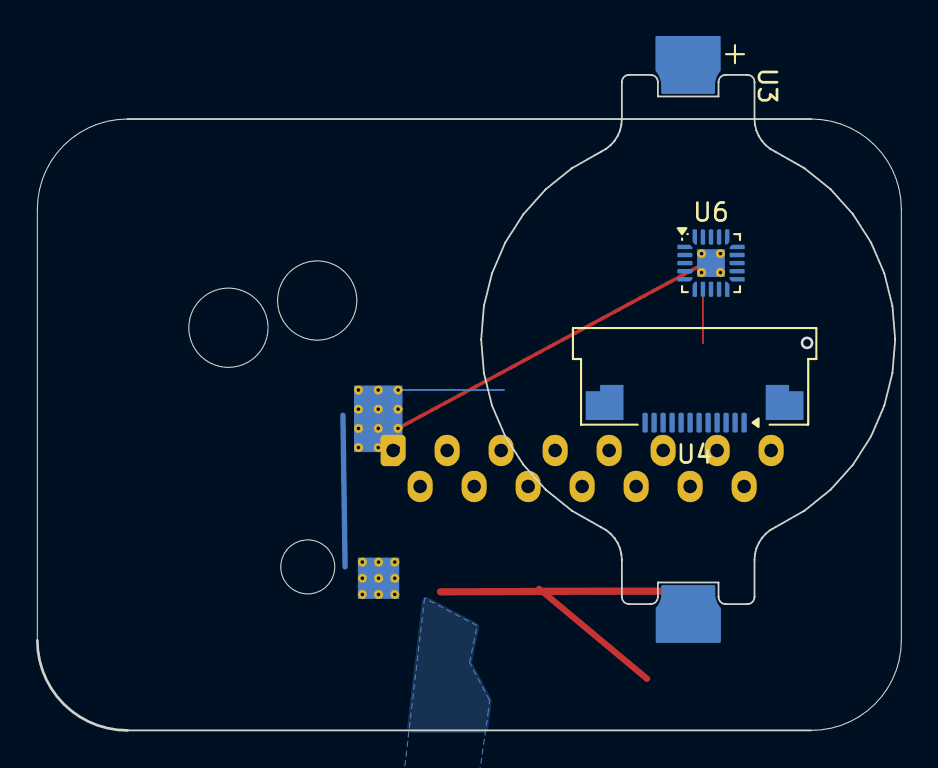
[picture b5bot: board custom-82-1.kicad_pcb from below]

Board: 2 copper layers, 48.0 x 36.4 mm, 11 parts (3 on the bottom side), 10 nets.

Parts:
U1: VQFN-48-1EP_7x7mm_P0.5mm_EP2.6x2.6mm_ThermalVias
U2: Mounting_Wuerth_WA-SMSSR-3.3mm_H8mm_SnapRivet_977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; Mounting_Wuerth_WA-SMSSR-3.3mm_H8mm_SnapRivet_9776080960
U3: BatteryHolder_Keystone_1057_1x2032
U4: Amphenol_F32Q-1A7x1-11012_1x12-1MP_P0.5mm_Horizon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; Amphenol_F32Q-1A7x1-11012_1x12-1MP_P0.5mm_Horizontal
U5: TQFN-32-1EP_5x5mm_P0.5mm_EP2.1x2.1mm
U6: VQFN-20-1EP_3x3mm_P0.45mm_EP1.55x1.55mm_ThermalVi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; VQFN-20-1EP_3x3mm_P0.45mm_EP1.55x1.55mm_ThermalVias
U7: Mounting_Wuerth_WA-SMST-3.3mm_H1.5mm_9774015960
U8: Vishay_PowerPAK_SC70-6L_Single
U9: Texas_REE0036A_WQFN-36-1EP_4x5mm_P0.4mm_EP2.7x3.7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; Texas_REE0036A_WQFN-36-1EP_4x5mm_P0.4mm_EP2.7x3.7mm_Thermal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
U10: Mounting_Wuerth_WA-SMSI-M2_H2mm_9774020243
U11: JST_ZE_B15B-ZESK-D_1x15_P1.50mm_Vertical

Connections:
/sub/clk: U1.8, U1.10, U1.14, U1.22, U1.36, U1.39, U1.41, U3.1, U4.2, U5.1, U5.5, U5.10, U5.21, U5.23, U6.21, U8.1, U8.3, U9.8, U9.15, U9.30, U9.36, U11.7
D7: U1.3, U1.9, U1.18, U1.21, U1.27, U1.49, U4.MP, U5.20, U5.33, U7.1, U8.4, U9.6, U9.35, U9.37, U10.1, U11.4, U11.10
D12: U1.5, U1.13, U1.17, U1.19, U1.49, U6.21, U9.9, U9.10, U9.37, U11.14
GND: U1.2, U3.2, U4.1, U4.5, U4.11, U5.19, U5.26, U6.4, U6.11, U6.14, U6.18, U7.1, U9.16, U9.22, U9.32, U9.37, U11.1
N2: U1.32, U1.42, U1.49, U4.3, U4.7, U4.8, U5.4, U5.29, U5.32, U6.19, U9.21, U9.26, U11.6, U11.13
N3: U1.29, U1.44, U1.47, U1.48, U4.4, U4.6, U5.9, U5.15, U6.20, U6.21, U7.1, U9.37
PWR1: U1.4, U1.6, U1.7, U1.16, U1.24, U1.45, U1.49, U2.1, U5.2, U5.3, U5.14, U5.24, U5.30, U6.5, U6.9, U6.21, U9.3, U9.14, U9.17, U9.18, U9.28, U9.34, U9.37, U10.1
PWR_5V: U1.15, U5.11, U5.25, U5.27, U6.1, U6.3, U6.12, U7.1, U8.4, U9.4, U9.31, U9.37
SIG1: U1.30, U1.35, U2.1, U5.16, U5.17, U5.31, U6.8, U6.10, U9.5, U9.7, U9.23, U9.33, U11.2
VCC: U1.1, U1.23, U1.25, U1.26, U1.33, U1.34, U6.13, U6.17, U9.1, U9.12, U9.25, U9.37, U11.5, U11.9

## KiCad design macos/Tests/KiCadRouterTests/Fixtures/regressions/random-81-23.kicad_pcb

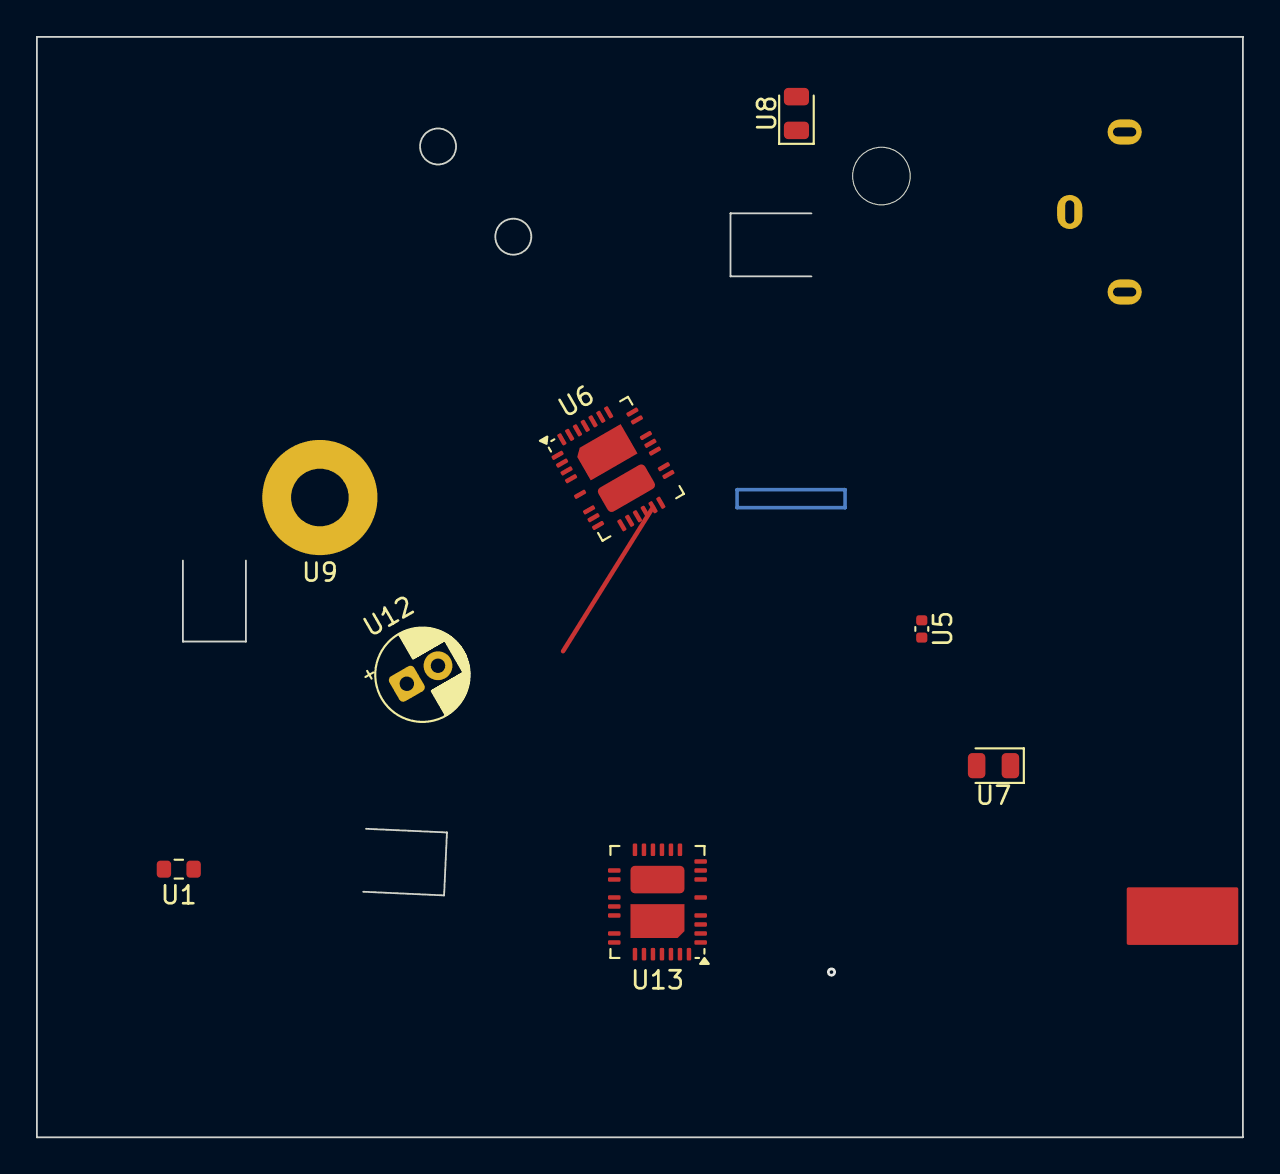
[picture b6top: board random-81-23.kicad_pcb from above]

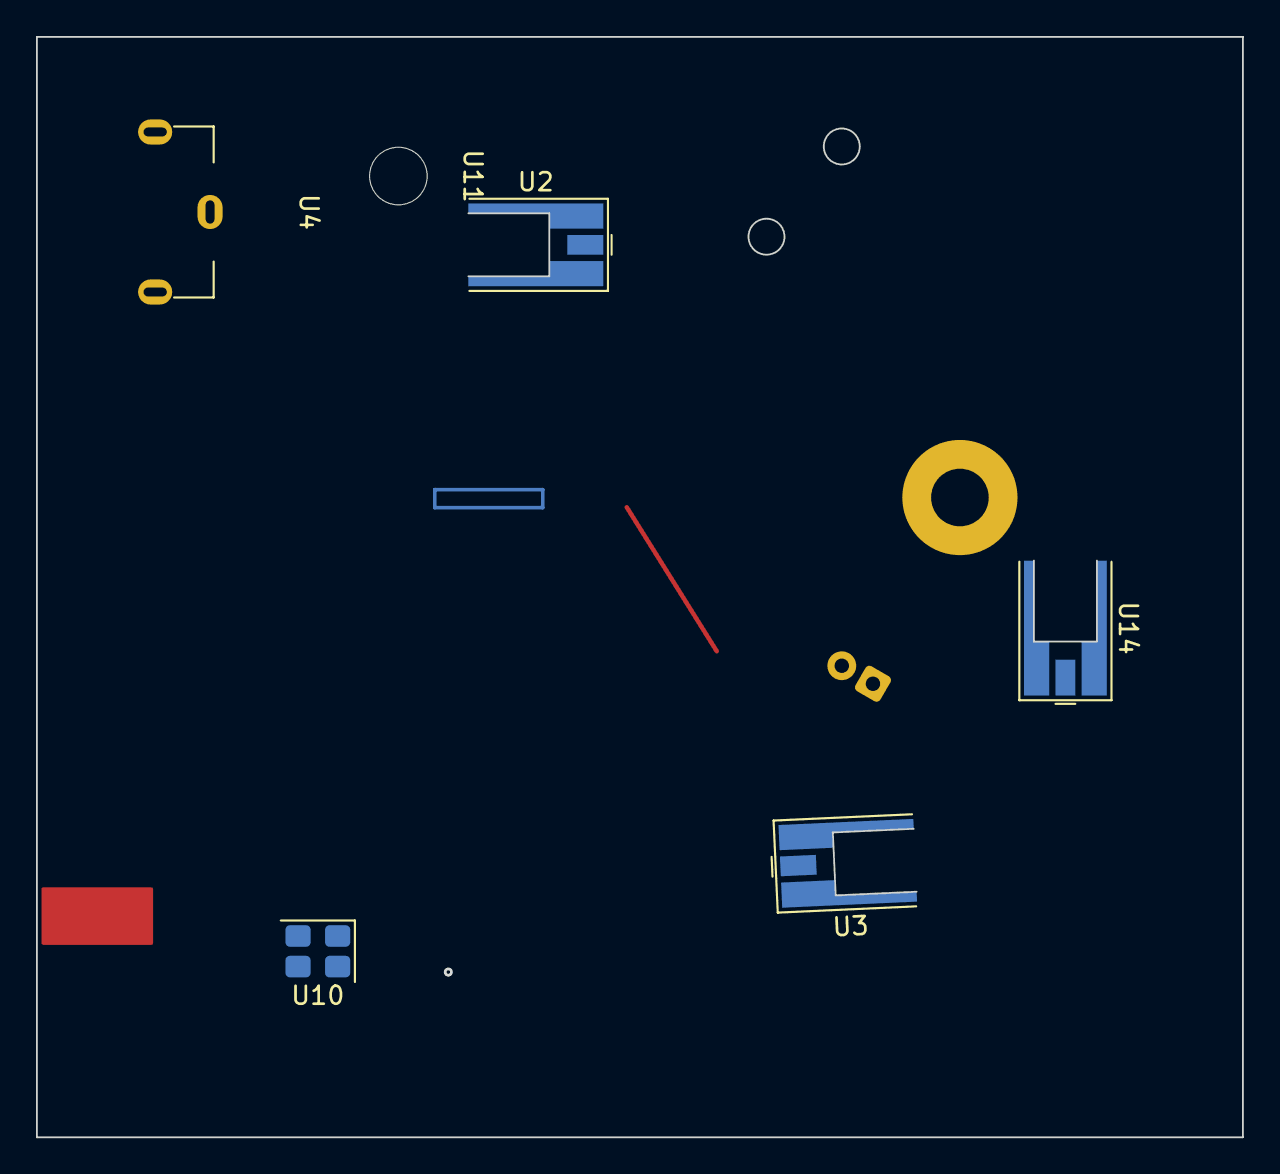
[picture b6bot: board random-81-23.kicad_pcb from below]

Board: 2 copper layers, 67.0 x 61.1 mm, 14 parts (6 on the bottom side), 6 nets.

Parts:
U1: R_0603_1608Metric
U2, U3, U14: MMCX_Molex_73415-0961_Horizontal_0.8mm-PCB
U4: BatteryHolder_Keystone_590
U5: C_0402_1005Metric
U6, U13: Analog_QFN-28-36-2EP_5x6mm_P0.5mm
U7, U8: LED_0805_2012Metric
U9: MountingHole_3.2mm_M3_Pad
U10: Crystal_SMD_3225-4Pin_3.2x2.5mm
U11: MountingHole_3.2mm_M3
U12: CP_Radial_D5.0mm_P2.00mm

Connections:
/sub/clk: U2.2, U6.1, U6.2, U6.8, U6.10, U6.13, U6.27, U7.1, U10.1, U13.3, U13.21, U13.23, U13.33, U13.36, U14.1
N2: U5.2, U6.21, U6.28, U9.1, U10.4, U13.4, U13.32, U13.34
N3: U2.2, U3.1, U4.1, U6.17, U6.33, U10.2, U13.1, U13.20, U13.24
PWR1: U3.2, U5.1, U6.12, U6.32, U8.2, U14.2
SIG1: U2.1, U4.1, U6.3, U6.15, U6.31, U8.1, U10.3, U13.2, U13.6, U13.8, U13.12, U13.16, U13.27, U13.28
VCC: U6.4, U6.24, U6.35, U6.36, U6.37, U6.38, U13.13, U13.25, U13.37, U13.38

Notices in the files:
README.md:
maven-license-plugin:
mvn license:check
mvn license:format
mvn license:remove
